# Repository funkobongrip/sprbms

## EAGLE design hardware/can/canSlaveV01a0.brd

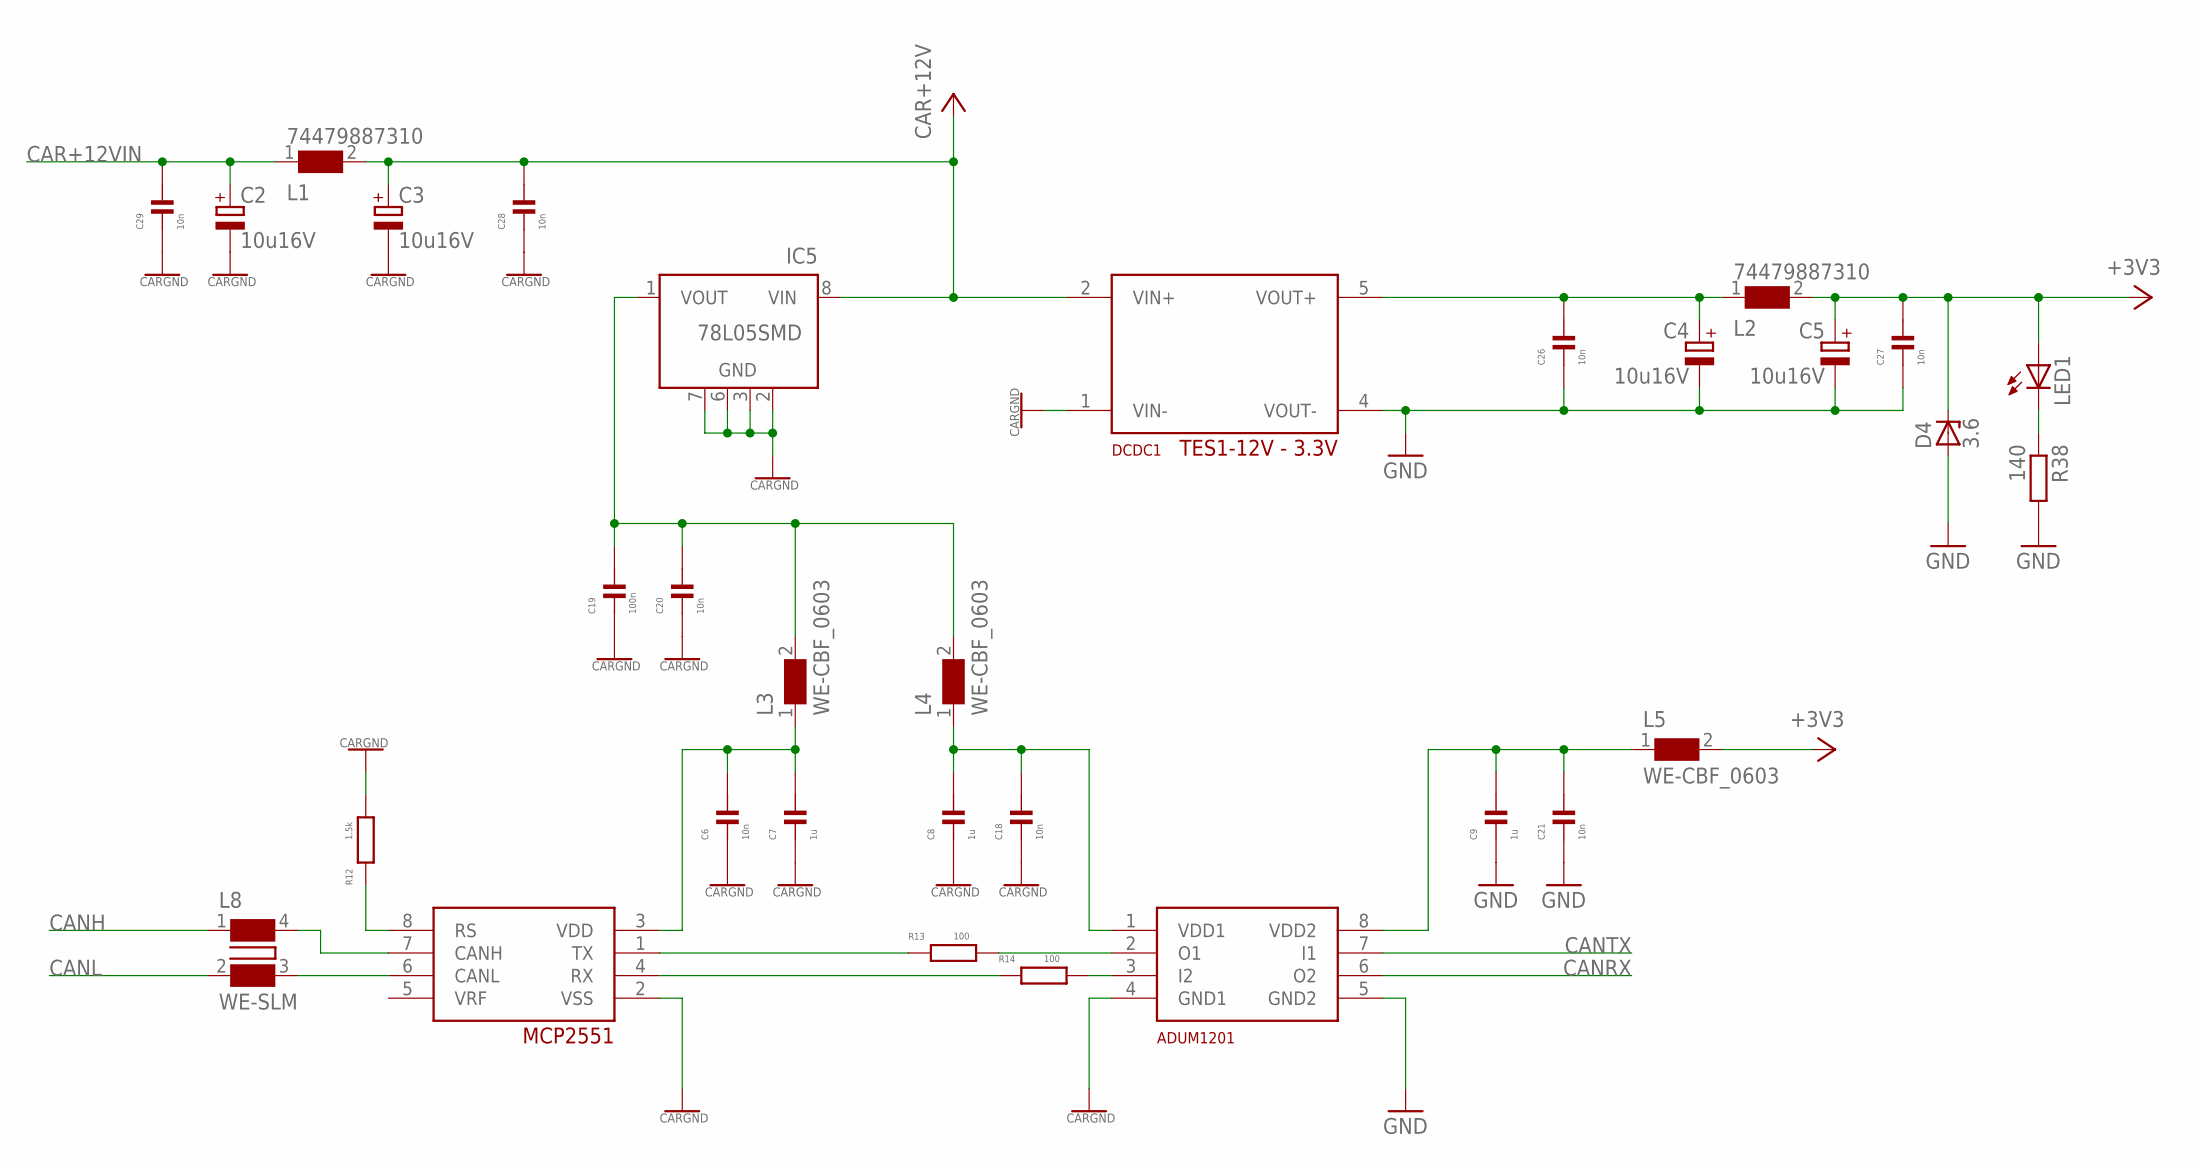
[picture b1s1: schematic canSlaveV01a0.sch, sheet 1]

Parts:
C2, C3, C4, C5: 10u16V; PANASONIC_B
C6, C18, C20, C21, C26, C27, C28, C29: 10n; C0603
C7, C8, C9: 1u; C0603
C19: 100n; C0603
D4: 3.6; SOD323-W
DCDC1: TES1-12V - 3.3V; ISF
IC3: ADUM1201; SO-8
IC4: MCP2551; SO-8
IC5: 78L05SMD; SO08
L1, L2: 74479887310; WE-PMI_1008
L3, L4, L5: WE-CBF_0603; 0603
L8: WE-SLM
LED1: LEDCHIPLED_1206; CHIPLED_1206
R12: 1.5k; R0603
R13, R14: 100; R0603
R38: 140; R1206

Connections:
+3V3: C5.+, C27.1, D4.C, L2.2, L5.2, LED1.A; also elsewhere on the board
+3V3DCOUT: C4.+, C26.1, DCDC1.5 (VOUT+), L2.1
+3V3_AD: C9.1, C21.1, IC3.8 (VDD2), L5.1
CANH: L8.1 (3); also elsewhere on the board
CANHC: IC4.7 (CANH), L8.4
CANL: L8.2 (1); also elsewhere on the board
CANLC: IC4.6 (CANL), L8.3 (2)
CANRX: IC3.6 (O2); also elsewhere on the board
CANTX: IC3.7 (I1); also elsewhere on the board
CAR+5V: C19.1, C20.1, IC5.1 (VOUT), L3.2, L4.2
CAR+5V_AD: C8.1, C18.1, IC3.1 (VDD1), L4.1
CAR+5V_CT: C6.1, C7.1, IC4.3 (VDD), L3.1
CAR+12V: C3.+, C28.1, DCDC1.2 (VIN+), IC5.8 (VIN), L1.2
CAR+12VIN: C2.+, C29.1, L1.1; also elsewhere on the board
CARGND: C2.-, C3.-, C6.2, C7.2, C8.2, C18.2, C19.2, C20.2, C28.2, C29.2, DCDC1.1 (VIN-), IC3.4 (GND1), IC4.2 (VSS), IC5.2 (GND), IC5.3 (GND), IC5.6 (GND), IC5.7 (GND), R12.2; also elsewhere on the board
CAR_CANRX: IC3.3 (I2), R14.2
CAR_CANRX_T: IC4.4 (RX), R14.1
CAR_CANTX: IC3.2 (O1), R13.2
CAR_CANTX_T: IC4.1 (TX), R13.1
GND: C4.-, C5.-, C9.2, C21.2, C26.2, C27.2, D4.A, DCDC1.4 (VOUT-), IC3.5 (GND2), R38.2; also elsewhere on the board
LED1C: LED1.C, R38.1
RS: IC4.8 (RS), R12.1

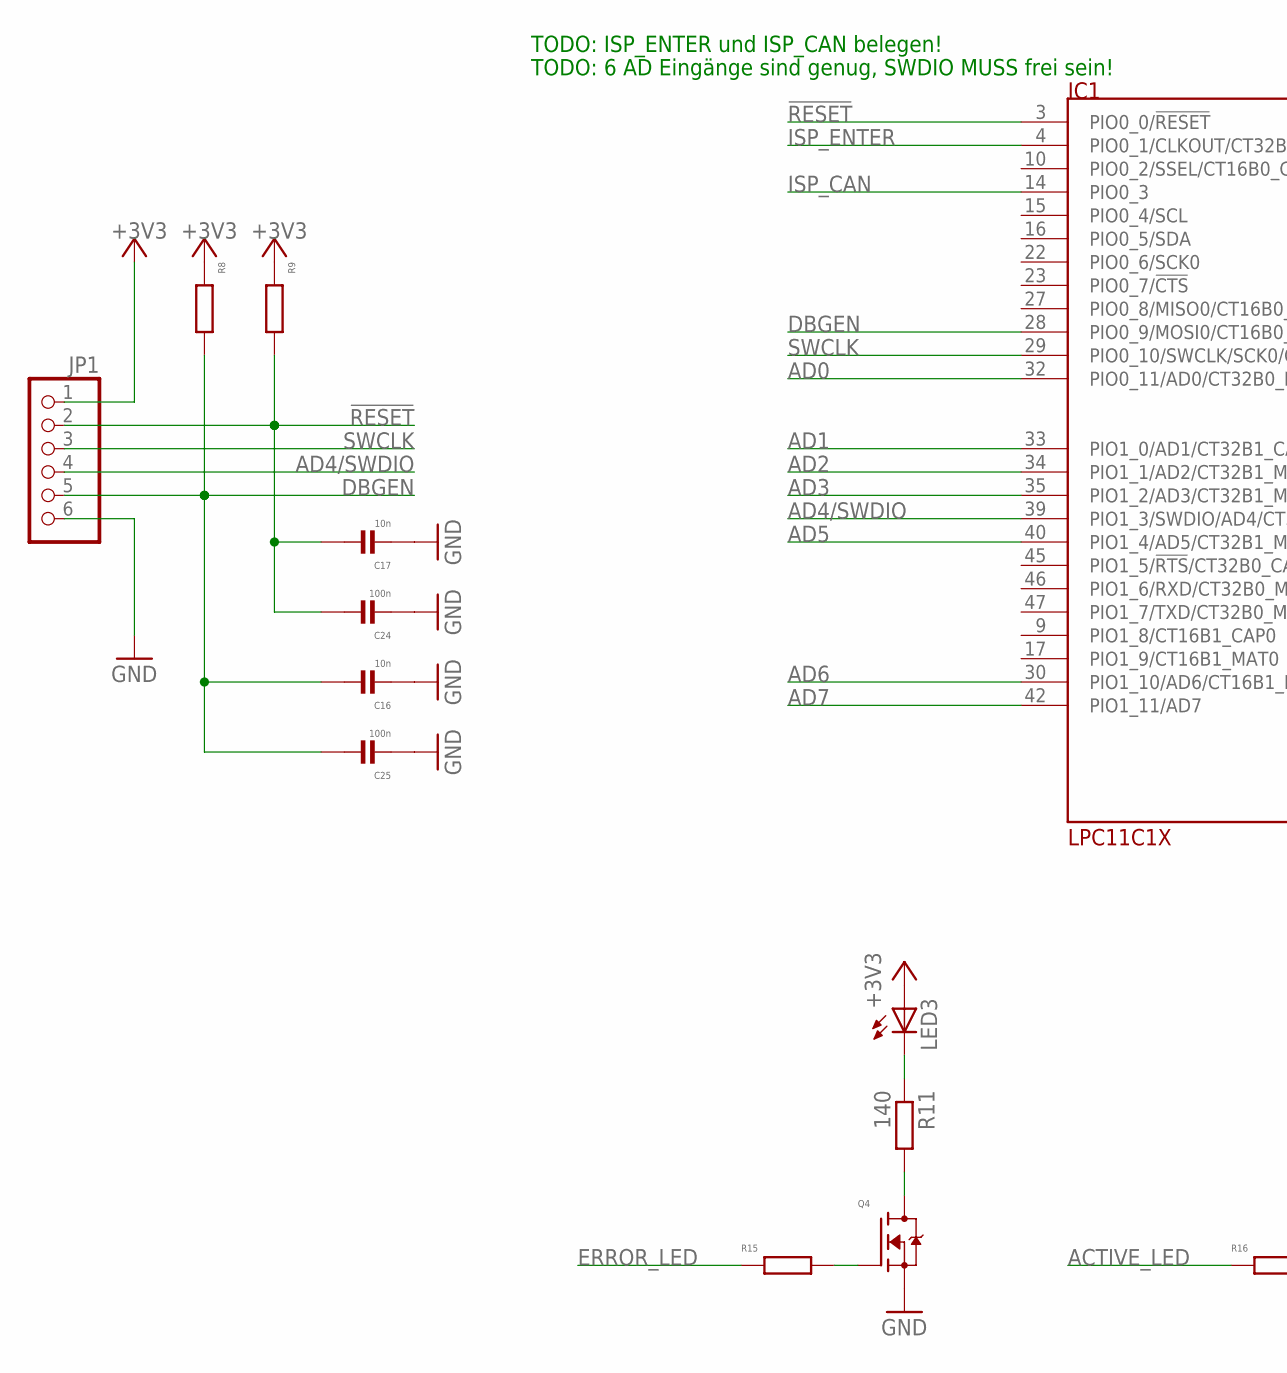
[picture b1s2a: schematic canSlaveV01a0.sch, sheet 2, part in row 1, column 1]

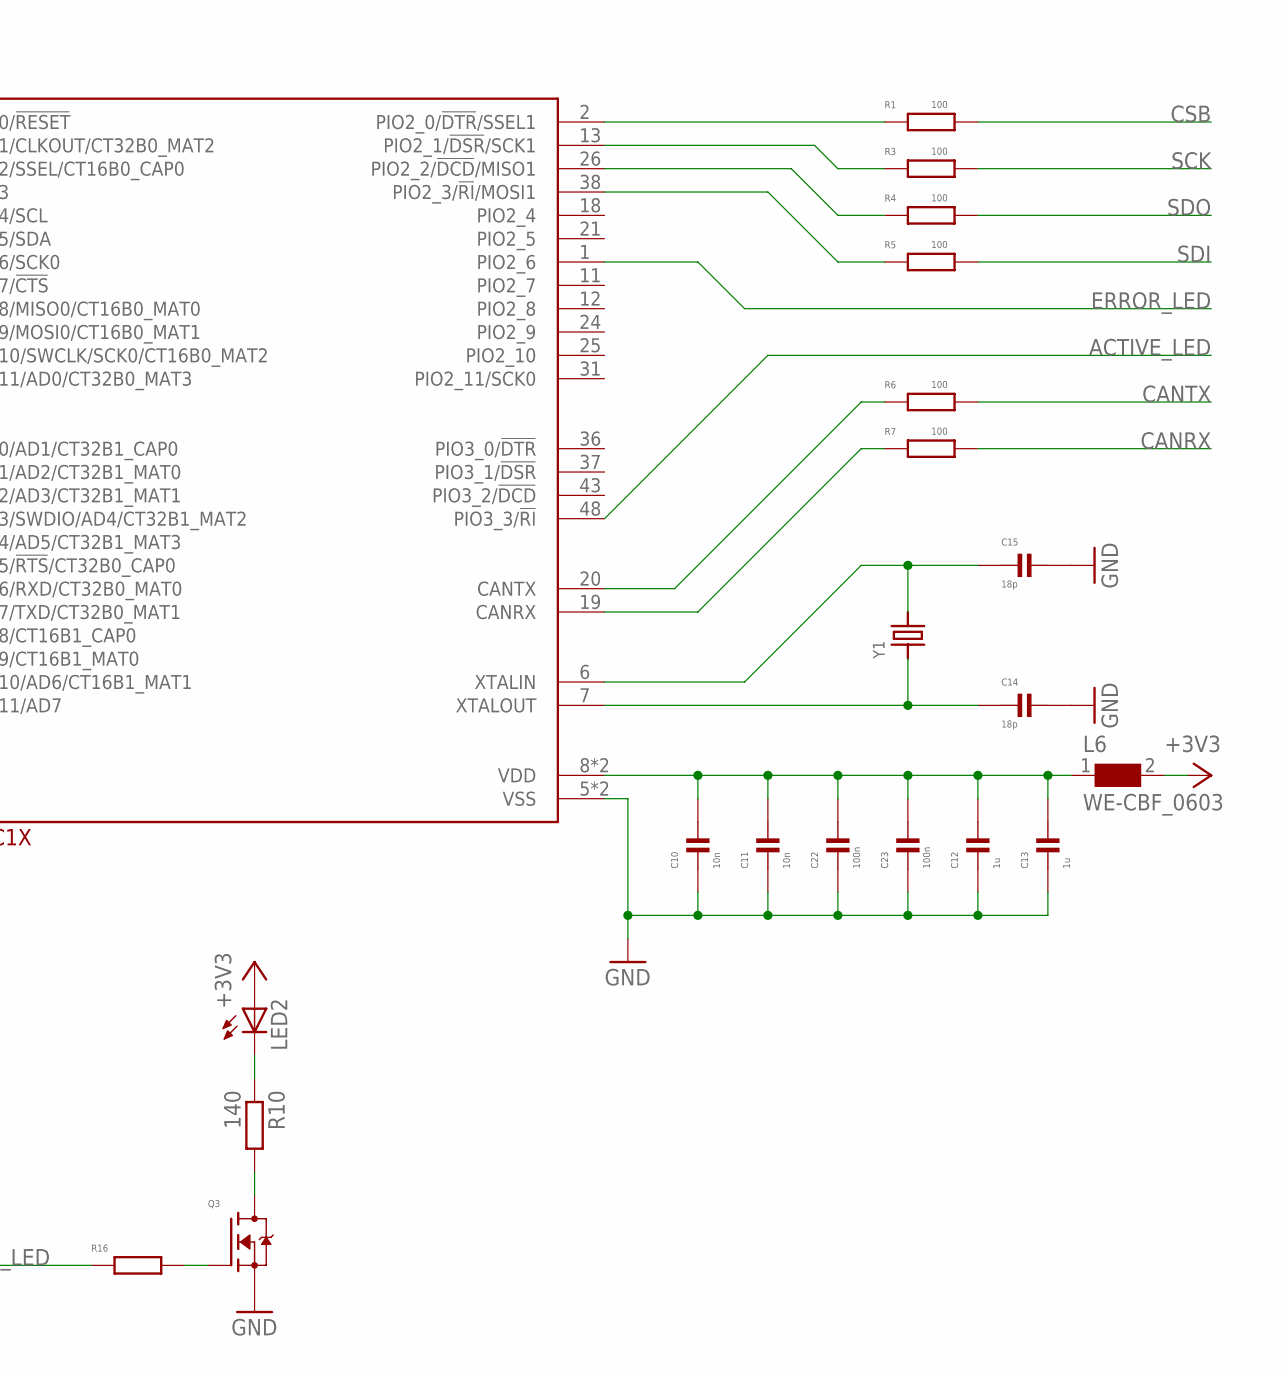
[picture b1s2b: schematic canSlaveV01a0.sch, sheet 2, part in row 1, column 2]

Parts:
C10, C11, C16, C17: 10n; C0603
C12, C13: 1u; C0603
C14, C15: 18p; C0603
C22, C23, C24, C25: 100n; C0603
IC1: LPC11C1X; LQFP48
JP1: PINHD-1X6; 1X06
L6: WE-CBF_0603; 0603
LED2, LED3: LEDCHIPLED_1206; CHIPLED_1206
Q3, Q4: 2N7002; SOT23
R1, R3, R4, R5, R6, R7: 100; R0603
R8, R9, R15, R16: R0603
R10, R11: 140; R1206
Y1: CRYSTALTHIN; CRYSTAL_3.2X2.5

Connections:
!RESET: C17.1, C24.1, IC1.3 (PIO0_0/!RESET), JP1.2, R9.2
+3V3: JP1.1, L6.2, LED2.A, LED3.A, R8.1, R9.1; also elsewhere on the board
+3V3_UC: C10.1, C11.1, C12.1, C13.1, C22.1, C23.1, IC1.8 (VDD), IC1.44 (VDD), L6.1
ACTIVE_LED: IC1.48 (PIO3_3/!RI), R16.1
ACTIVE_LED_G: Q3.1 (G), R16.2
AD0: IC1.32 (PIO0_11/AD0/CT32B0_MAT3); also elsewhere on the board
AD1: IC1.33 (PIO1_0/AD1/CT32B1_CAP0); also elsewhere on the board
AD2: IC1.34 (PIO1_1/AD2/CT32B1_MAT0); also elsewhere on the board
AD3: IC1.35 (PIO1_2/AD3/CT32B1_MAT1); also elsewhere on the board
AD4/SWDIO: IC1.39 (PIO1_3/SWDIO/AD4/CT32B1_MAT2), JP1.4; also elsewhere on the board
AD5: IC1.40 (PIO1_4/AD5/CT32B1_MAT3); also elsewhere on the board
AD6: IC1.30 (PIO1_10/AD6/CT16B1_MAT1); also elsewhere on the board
AD7: IC1.42 (PIO1_11/AD7); also elsewhere on the board
CANRX: R7.2; also elsewhere on the board
CANRX_U: IC1.19 (CANRX), R7.1
CANTX: R6.2; also elsewhere on the board
CANTX_U: IC1.20 (CANTX), R6.1
CSB: R1.2; also elsewhere on the board
DBGEN: C16.1, C25.1, IC1.28 (PIO0_9/MOSI0/CT16B0_MAT1), JP1.5, R8.2
ERROR_LED: IC1.1 (PIO2_6), R15.1
ERROR_LED_G: Q4.1 (G), R15.2
GND: C10.2, C11.2, C12.2, C13.2, C14.1, C15.1, C16.2, C17.2, C22.2, C23.2, C24.2, C25.2, IC1.5 (VSS), IC1.41 (VSS), JP1.6, Q3.2 (S), Q4.2 (S); also elsewhere on the board
ISP_CAN: IC1.14 (PIO0_3)
ISP_ENTER: IC1.4 (PIO0_1/CLKOUT/CT32B0_MAT2)
LED1C1: LED2.C, R10.1
LED1C2: LED3.C, R11.1
MISO1: IC1.26 (PIO2_2/!DCD!/MISO1), R4.1
MOSI1: IC1.38 (PIO2_3/!RI!/MOSI1), R5.1
Q3_COL: Q3.3 (D), R10.2
Q3_COL1: Q4.3 (D), R11.2
SCK: R3.2; also elsewhere on the board
SCK1: IC1.13 (PIO2_1/!DSR!/SCK1), R3.1
SDI: R5.2; also elsewhere on the board
SDO: R4.2; also elsewhere on the board
SSEL: IC1.2 (PIO2_0/!DTR!/SSEL1), R1.1
SWCLK: IC1.29 (PIO0_10/SWCLK/SCK0/CT16B0_MAT2), JP1.3
XTALIN: C15.2, IC1.6 (XTALIN), Y1.2
XTALOUT: C14.2, IC1.7 (XTALOUT), Y1.1

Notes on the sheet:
TODO: ISP_ENTER und ISP_CAN belegen!
TODO: 6 AD Eingänge sind genug, SWDIO MUSS frei sein!

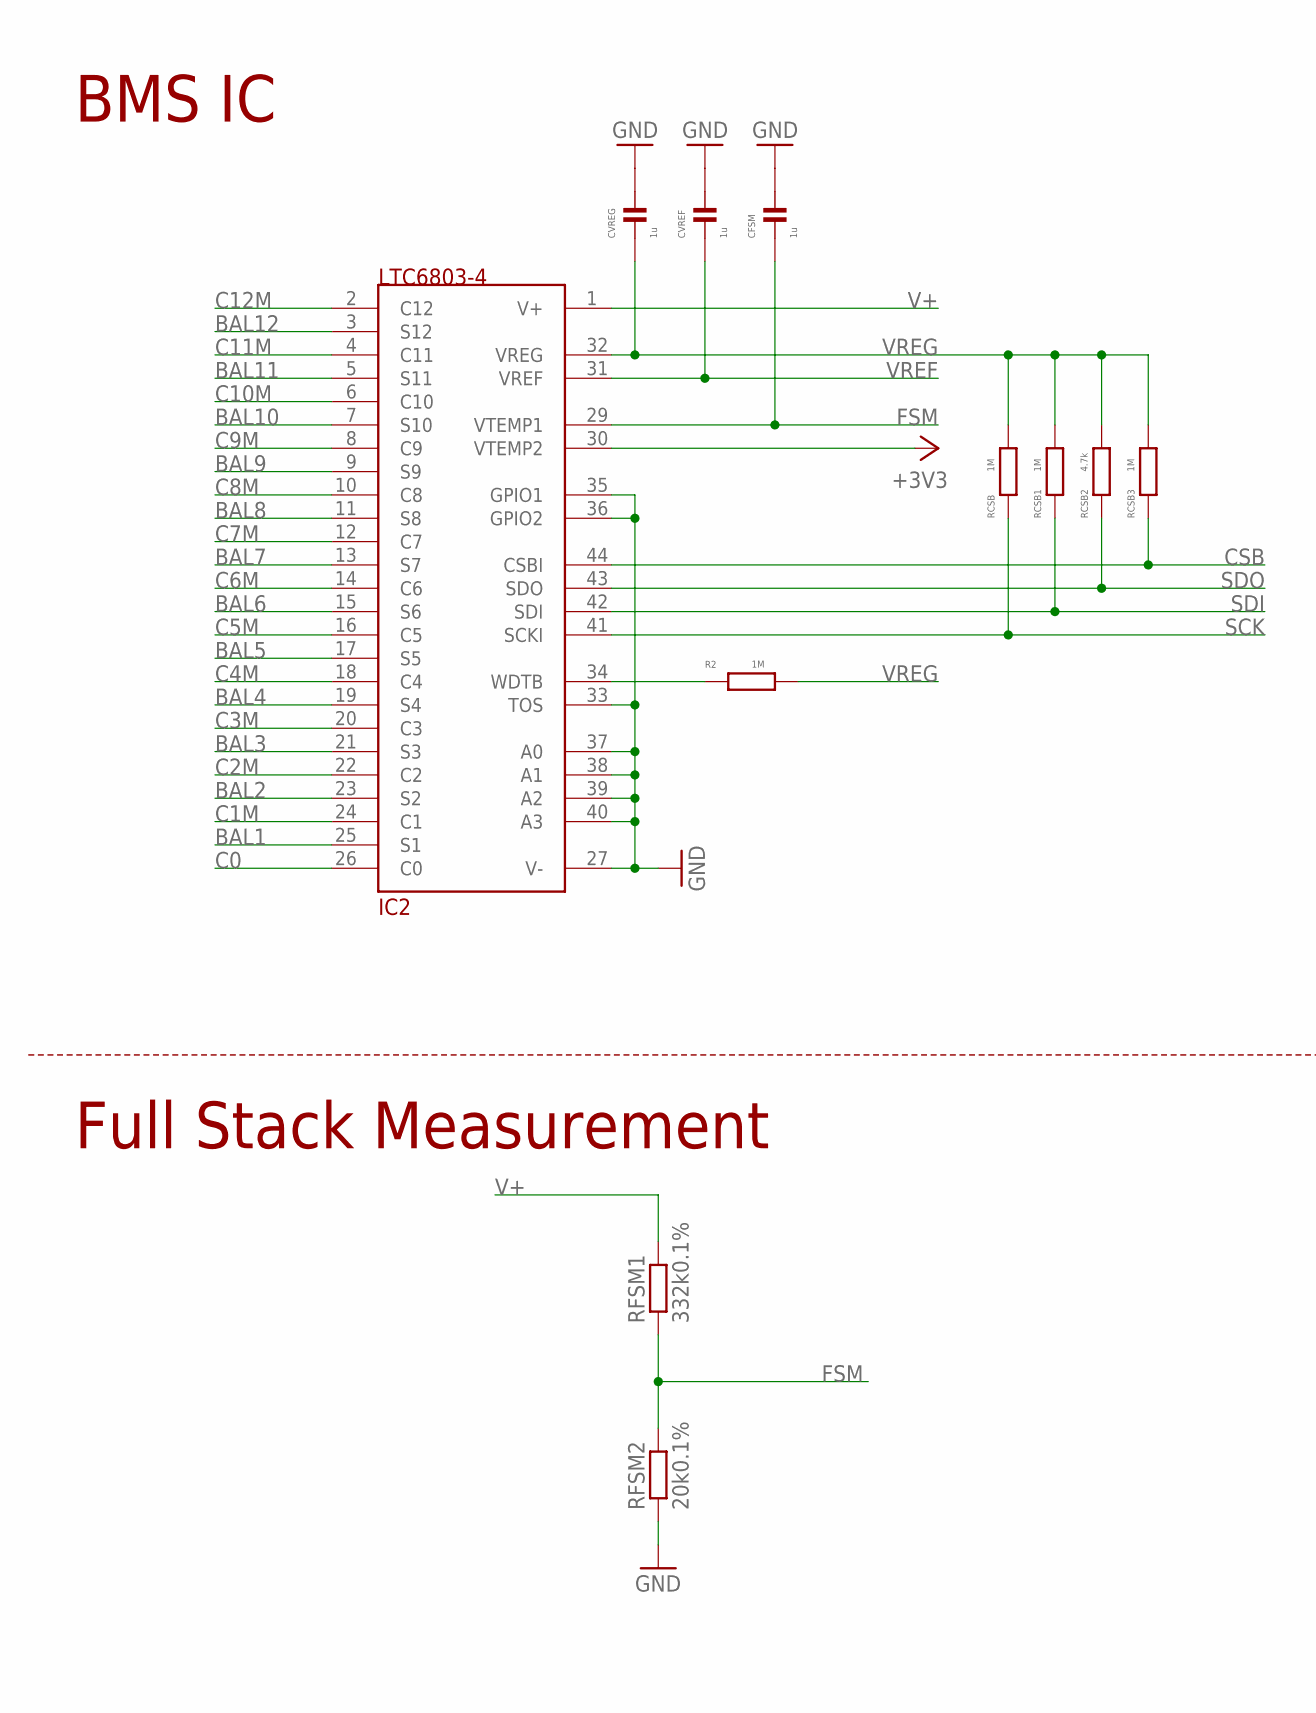
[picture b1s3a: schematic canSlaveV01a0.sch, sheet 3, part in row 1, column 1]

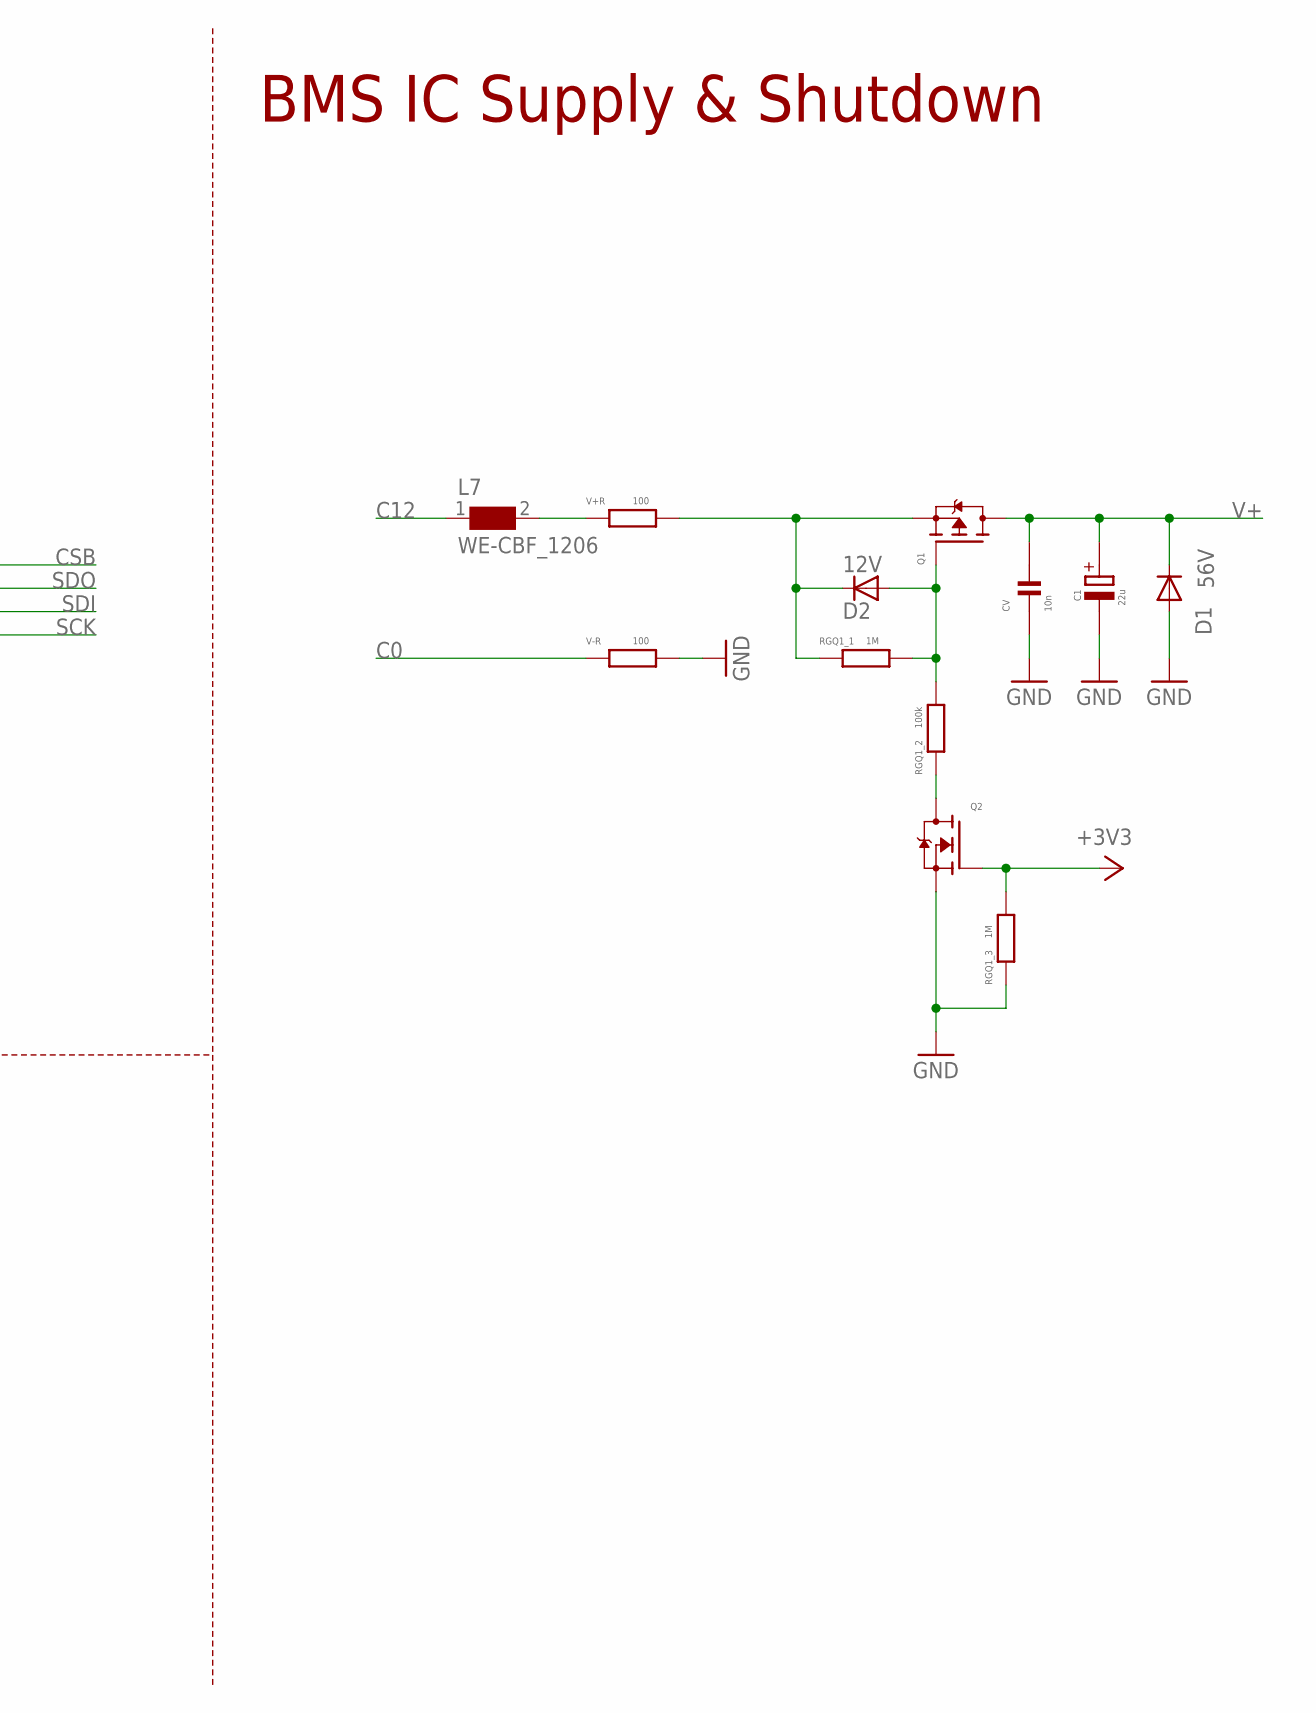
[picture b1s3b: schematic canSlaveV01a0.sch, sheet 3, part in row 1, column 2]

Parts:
C1: 22u; PANASONIC_F
CFSM: 1u; C0603
CV: 10n; C1206
CVREF: 1u; C0603
CVREG: 1u; C0603
D1: 56V; SOD123
D2: 12V; SOD323-R
IC2: LTC6803-4; 44SSOP
L7: WE-CBF_1206; 1206
Q1: TP0610K; SOT23
Q2: 2N7002; SOT23
R2: 1M; R0603
RCSB, RCSB1, RCSB3: 1M; R0603
RCSB2: 4.7k; R0603
RFSM1: 332k0.1%; R0603
RFSM2: 20k0.1%; R0603
RGQ1_1: 1M; R0805
RGQ1_2: 100k; R0805
RGQ1_3: 1M; R0603
V+R: 100; R0805
V-R: 100; R0805

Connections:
+3V3: IC2.30 (VTEMP2), Q2.1 (G), RGQ1_3.2; also elsewhere on the board
BAL1: IC2.25 (S1); also elsewhere on the board
BAL2: IC2.23 (S2); also elsewhere on the board
BAL3: IC2.21 (S3); also elsewhere on the board
BAL4: IC2.19 (S4); also elsewhere on the board
BAL5: IC2.17 (S5); also elsewhere on the board
BAL6: IC2.15 (S6); also elsewhere on the board
BAL7: IC2.13 (S7); also elsewhere on the board
BAL8: IC2.11 (S8); also elsewhere on the board
BAL9: IC2.9 (S9); also elsewhere on the board
BAL10: IC2.7 (S10); also elsewhere on the board
BAL11: IC2.5 (S11); also elsewhere on the board
BAL12: IC2.3 (S12); also elsewhere on the board
C0: IC2.26 (C0), V-R.1; also elsewhere on the board
C1M: IC2.24 (C1); also elsewhere on the board
C2M: IC2.22 (C2); also elsewhere on the board
C3M: IC2.20 (C3); also elsewhere on the board
C4M: IC2.18 (C4); also elsewhere on the board
C5M: IC2.16 (C5); also elsewhere on the board
C6M: IC2.14 (C6); also elsewhere on the board
C7M: IC2.12 (C7); also elsewhere on the board
C8M: IC2.10 (C8); also elsewhere on the board
C9M: IC2.8 (C9); also elsewhere on the board
C10M: IC2.6 (C10); also elsewhere on the board
C11M: IC2.4 (C11); also elsewhere on the board
C12: L7.1; also elsewhere on the board
C12F: L7.2, V+R.1
C12M: IC2.2 (C12); also elsewhere on the board
CSB: IC2.44 (CSBI), RCSB3.1; also elsewhere on the board
FSM: CFSM.2, IC2.29 (VTEMP1), RFSM1.1, RFSM2.2
GND: C1.-, CFSM.1, CV.2, CVREF.1, CVREG.1, D1.A, IC2.27 (V-), IC2.33 (TOS), IC2.35 (GPIO1), IC2.36 (GPIO2), IC2.37 (A0), IC2.38 (A1), IC2.39 (A2), IC2.40 (A3), Q2.2 (S), RFSM2.1, RGQ1_3.1, V-R.2; also elsewhere on the board
Q1G: D2.A, Q1.1 (G), RGQ1_1.2, RGQ1_2.2
Q2D: Q2.3 (D), RGQ1_2.1
SCK: IC2.41 (SCKI), RCSB.1; also elsewhere on the board
SDI: IC2.42 (SDI), RCSB1.1; also elsewhere on the board
SDO: IC2.43 (SDO), RCSB2.1; also elsewhere on the board
V+: C1.+, CV.1, D1.C, IC2.1 (V+), Q1.3 (D), RFSM1.2
V+S: D2.C, Q1.2 (S), RGQ1_1.1, V+R.2
VREF: CVREF.2, IC2.31 (VREF)
VREG: CVREG.2, IC2.32 (VREG), R2.2, RCSB.2, RCSB1.2, RCSB2.2, RCSB3.2
WDTB: IC2.34 (WDTB), R2.1

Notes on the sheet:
BMS IC
BMS IC Supply & Shutdown
Full Stack Measurement

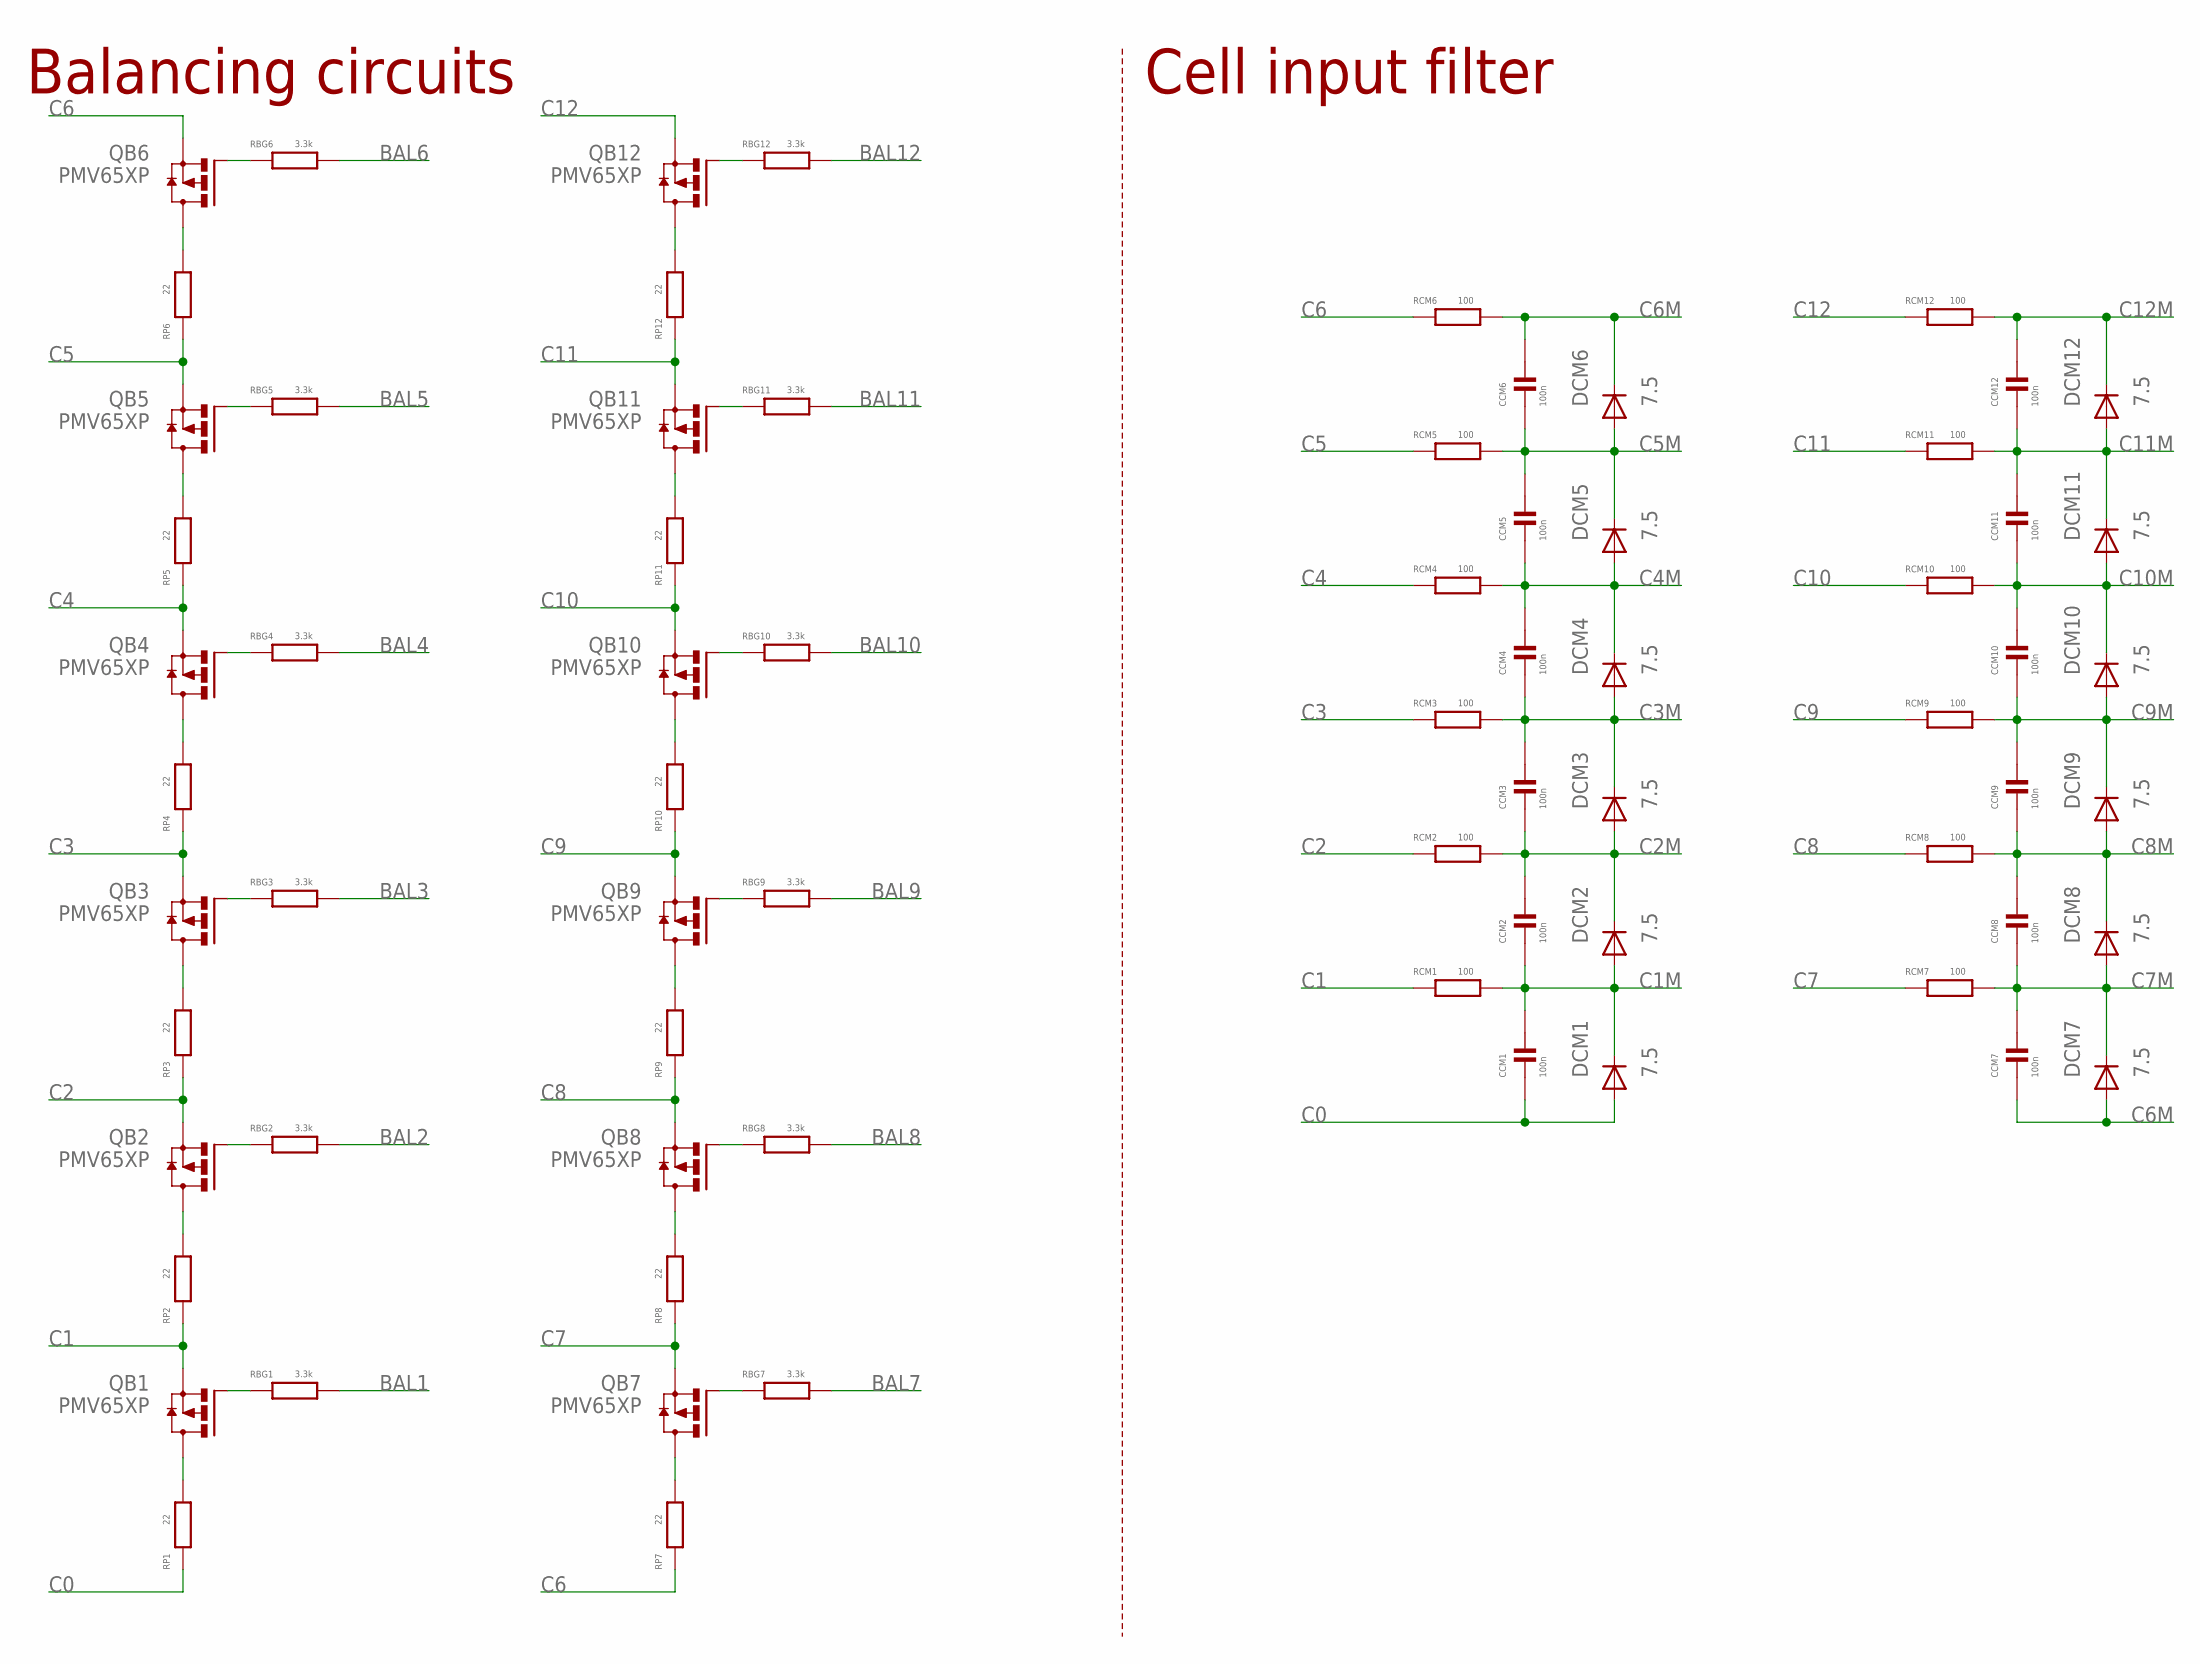
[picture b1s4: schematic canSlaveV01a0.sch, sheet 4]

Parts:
CCM1, CCM2, CCM3, CCM4, CCM5, CCM6, CCM7, CCM8, CCM9, CCM10, CCM11, CCM12: 100n; C0603
DCM1, DCM2, DCM3, DCM4, DCM5, DCM6, DCM7, DCM8, DCM9, DCM10, DCM11, DCM12: 7.5; SOD323-R
QB1, QB2, QB3, QB4, QB5, QB6, QB7, QB8, QB9, QB10, QB11, QB12: PMV65XP; SUPER-SOT3
RBG1, RBG2, RBG3, RBG4, RBG5, RBG6, RBG7, RBG8, RBG9, RBG10, RBG11, RBG12: 3.3k; R0603
RCM1, RCM2, RCM3, RCM4, RCM5, RCM6, RCM7, RCM8, RCM9, RCM10, RCM11, RCM12: 100; R0603
RP1, RP2, RP3, RP4, RP5, RP6, RP7, RP8, RP9, RP10, RP11, RP12: 22; R2512

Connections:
BAL1: RBG1.2; also elsewhere on the board
BAL2: RBG2.2; also elsewhere on the board
BAL3: RBG3.2; also elsewhere on the board
BAL4: RBG4.2; also elsewhere on the board
BAL5: RBG5.2; also elsewhere on the board
BAL6: RBG6.2; also elsewhere on the board
BAL7: RBG7.2; also elsewhere on the board
BAL8: RBG8.2; also elsewhere on the board
BAL9: RBG9.2; also elsewhere on the board
BAL10: RBG10.2; also elsewhere on the board
BAL11: RBG11.2; also elsewhere on the board
BAL12: RBG12.2; also elsewhere on the board
C0: CCM1.2, DCM1.A, RP1.1; also elsewhere on the board
C1: QB1.2 (S), RCM1.1, RP2.1; also elsewhere on the board
C1M: CCM1.1, CCM2.2, DCM1.C, DCM2.A, RCM1.2; also elsewhere on the board
C2: QB2.2 (S), RCM2.1, RP3.1; also elsewhere on the board
C2M: CCM2.1, CCM3.2, DCM2.C, DCM3.A, RCM2.2; also elsewhere on the board
C3: QB3.2 (S), RCM3.1, RP4.1; also elsewhere on the board
C3M: CCM3.1, CCM4.2, DCM3.C, DCM4.A, RCM3.2; also elsewhere on the board
C4: QB4.2 (S), RCM4.1, RP5.1; also elsewhere on the board
C4M: CCM4.1, CCM5.2, DCM4.C, DCM5.A, RCM4.2; also elsewhere on the board
C5: QB5.2 (S), RCM5.1, RP6.1; also elsewhere on the board
C5M: CCM5.1, CCM6.2, DCM5.C, DCM6.A, RCM5.2; also elsewhere on the board
C6: QB6.2 (S), RCM6.1, RP7.1; also elsewhere on the board
C6M: CCM6.1, CCM7.2, DCM6.C, DCM7.A, RCM6.2; also elsewhere on the board
C7: QB7.2 (S), RCM7.1, RP8.1; also elsewhere on the board
C7M: CCM7.1, CCM8.2, DCM7.C, DCM8.A, RCM7.2; also elsewhere on the board
C8: QB8.2 (S), RCM8.1, RP9.1; also elsewhere on the board
C8M: CCM8.1, CCM9.2, DCM8.C, DCM9.A, RCM8.2; also elsewhere on the board
C9: QB9.2 (S), RCM9.1, RP10.1; also elsewhere on the board
C9M: CCM9.1, CCM10.2, DCM9.C, DCM10.A, RCM9.2; also elsewhere on the board
C10: QB10.2 (S), RCM10.1, RP11.1; also elsewhere on the board
C10M: CCM10.1, CCM11.2, DCM10.C, DCM11.A, RCM10.2; also elsewhere on the board
C11: QB11.2 (S), RCM11.1, RP12.1; also elsewhere on the board
C11M: CCM11.1, CCM12.2, DCM11.C, DCM12.A, RCM11.2; also elsewhere on the board
C12: QB12.2 (S), RCM12.1; also elsewhere on the board
C12M: CCM12.1, DCM12.C, RCM12.2; also elsewhere on the board
CR1: QB1.3 (D), RP1.2
CR2: QB2.3 (D), RP2.2
CR3: QB3.3 (D), RP3.2
CR4: QB4.3 (D), RP4.2
CR5: QB5.3 (D), RP5.2
CR6: QB6.3 (D), RP6.2
CR7: QB7.3 (D), RP7.2
CR8: QB8.3 (D), RP8.2
CR9: QB9.3 (D), RP9.2
CR10: QB10.3 (D), RP10.2
CR11: QB11.3 (D), RP11.2
CR12: QB12.3 (D), RP12.2
QBG1: QB1.1 (G), RBG1.1
QBG2: QB2.1 (G), RBG2.1
QBG3: QB3.1 (G), RBG3.1
QBG4: QB4.1 (G), RBG4.1
QBG5: QB5.1 (G), RBG5.1
QBG6: QB6.1 (G), RBG6.1
QBG7: QB7.1 (G), RBG7.1
QBG8: QB8.1 (G), RBG8.1
QBG9: QB9.1 (G), RBG9.1
QBG10: QB10.1 (G), RBG10.1
QBG11: QB11.1 (G), RBG11.1
QBG12: QB12.1 (G), RBG12.1

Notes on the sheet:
Balancing circuits
Cell input filter

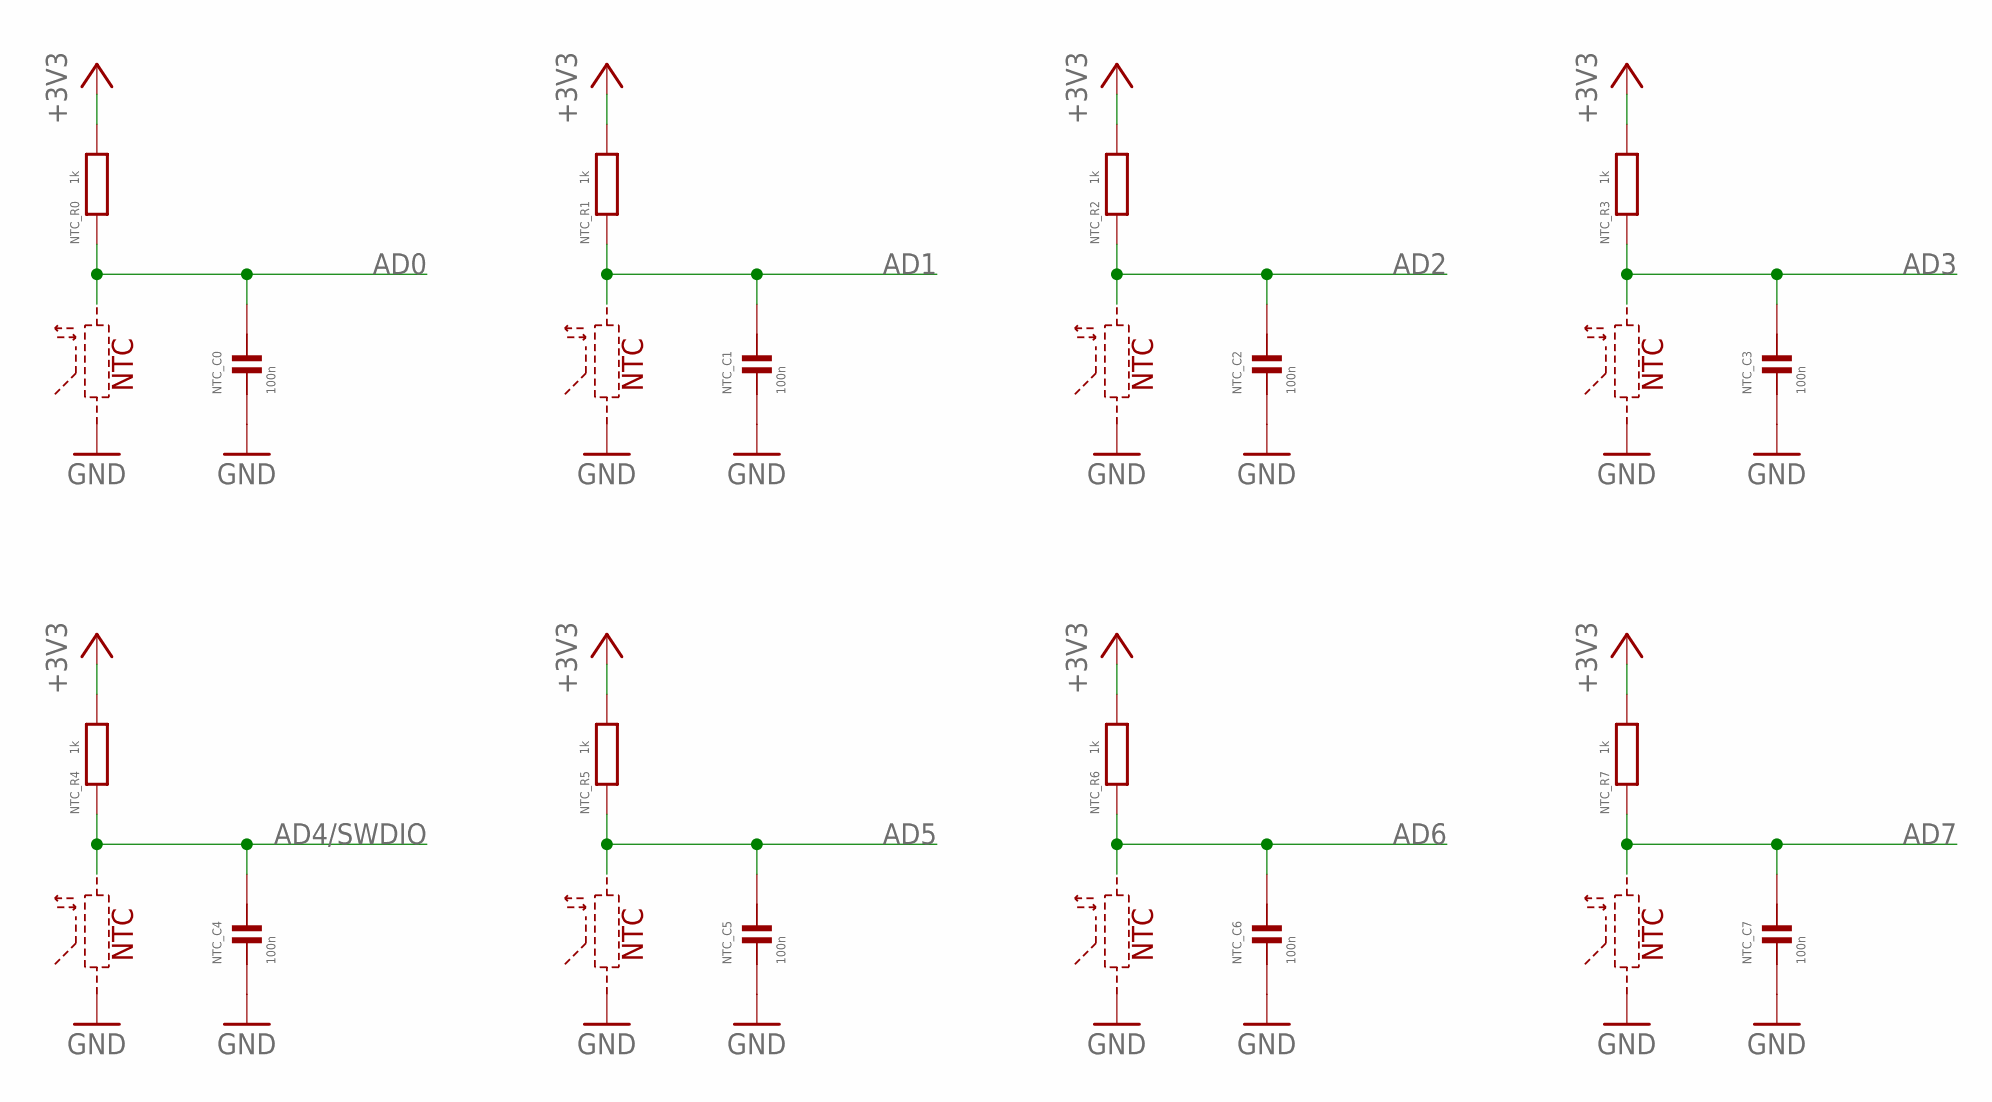
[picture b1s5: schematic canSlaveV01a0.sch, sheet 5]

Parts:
NTC_C0, NTC_C1, NTC_C2, NTC_C3, NTC_C4, NTC_C5, NTC_C6, NTC_C7: 100n; C0603
NTC_R0, NTC_R1, NTC_R2, NTC_R3, NTC_R4, NTC_R5, NTC_R6, NTC_R7: 1k; R0603

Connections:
+3V3: NTC_R0.2, NTC_R1.2, NTC_R2.2, NTC_R3.2, NTC_R4.2, NTC_R5.2, NTC_R6.2, NTC_R7.2; also elsewhere on the board
AD0: NTC_C0.1, NTC_R0.1; also elsewhere on the board
AD1: NTC_C1.1, NTC_R1.1; also elsewhere on the board
AD2: NTC_C2.1, NTC_R2.1; also elsewhere on the board
AD3: NTC_C3.1, NTC_R3.1; also elsewhere on the board
AD4/SWDIO: NTC_C4.1, NTC_R4.1; also elsewhere on the board
AD5: NTC_C5.1, NTC_R5.1; also elsewhere on the board
AD6: NTC_C6.1, NTC_R6.1; also elsewhere on the board
AD7: NTC_C7.1, NTC_R7.1; also elsewhere on the board
GND: NTC_C0.2, NTC_C1.2, NTC_C2.2, NTC_C3.2, NTC_C4.2, NTC_C5.2, NTC_C6.2, NTC_C7.2; also elsewhere on the board

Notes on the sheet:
NTC

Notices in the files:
hardware/can/canSlaveV05a_nutzen.brd:
CC BY-NC-SA
hardware/master/masterV05a.brd:
Licensed under: CC BY-NC-SA 3.0
distribute the resulting work only under the same or similar license
Full License: http://creativecommons.org/licenses/by-nc-sa/3.0/ or on Page 9 of Schematic
Copyright (C) 2012 David Brandt
parts and their libraries:
EagleLibrary_Wuerth_Elektronik_eiSos_Ver: Copyright: Würth Elektronik
microbuilder: This work is placed in the public domain, and may be freely used for commercial and non-commercial work with the following conditions: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
phrenetic: All rights reserved
